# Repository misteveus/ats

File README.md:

# ats

## Remote
- 3.3v power and ground header
    - No OVP
    - No OCP
    - No polarity protection
    - Modules have their own decoupling caps
    - Modules have decoupling capacitors
- SPI header for LoRa module debug
- UART header for GPS module debug
- ICSP header for programming the PIC18
- LoRa module and SMD antenna
- GPS module and SMD antenna
- PIC18 controller
    - Controls SPI and UART

## References
Microcontroller PIC18F06Q40 [datasheet](https://ww1.microchip.com/downloads/aemDocuments/documents/MCU08/ProductDocuments/DataSheets/PIC18F06-16Q40-Data-Sheet-40002216D.pdf)  
LoRa Tranceiver RFM95W [datasheet](https://www.rfsolutions.co.uk/downloads/1463993415RFM95_96_97_98W.pdf)  
GPS/GLONASS Receiver YIC71009EBGG [datasheet](https://www.yic.com.tw/wp-content/uploads/2021/05/YIC71009EBGG.pdf)

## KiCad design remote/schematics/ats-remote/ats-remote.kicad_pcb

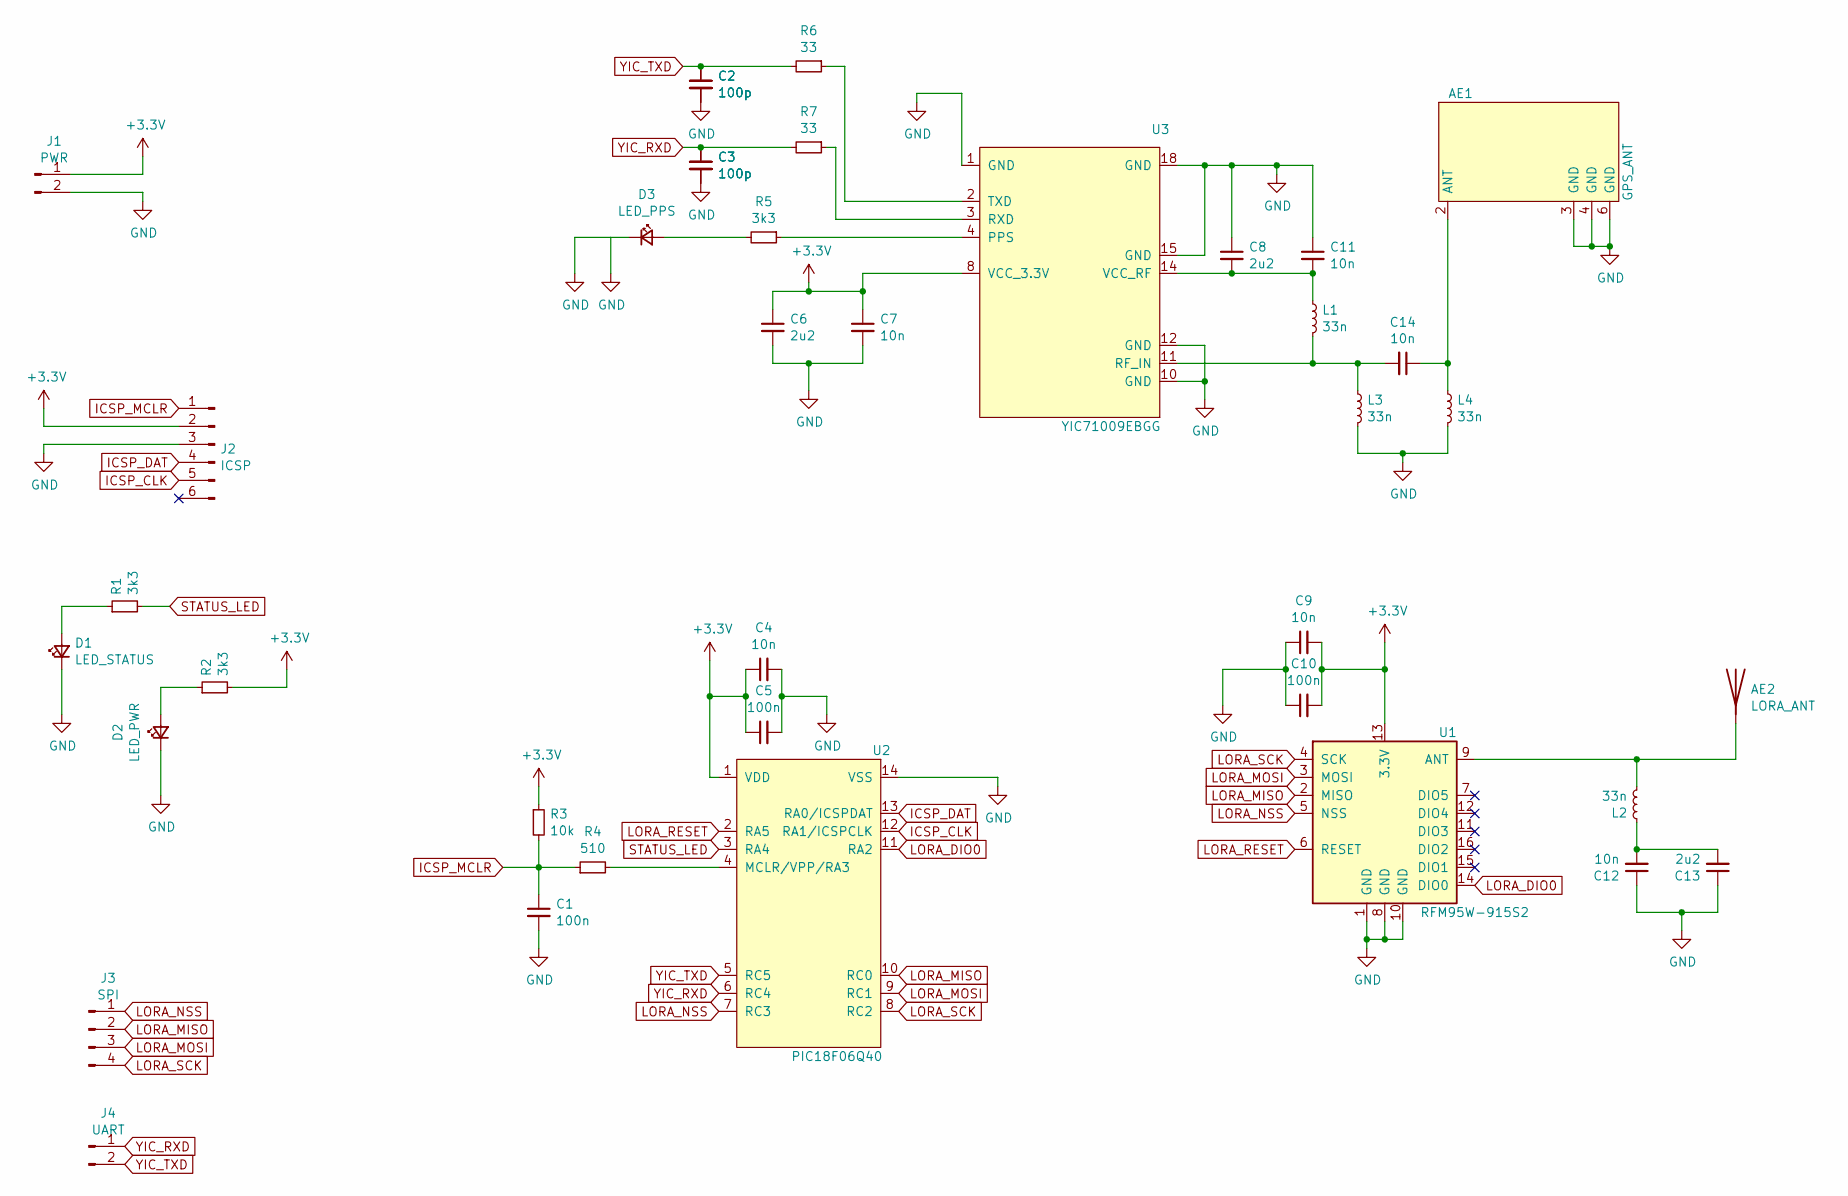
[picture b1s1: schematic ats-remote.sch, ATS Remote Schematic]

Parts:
AE1: GPS_ANT; GPS_ANT_SR4G008
AE2: LORA_ANT; LORA_ANT_YIC71009EBGG
C1, C5, C10: 100n; C_0805_2012Metric_Pad1.18x1.45mm_HandSolder
C2, C3: 100p; C_0805_2012Metric_Pad1.18x1.45mm_HandSolder
C4, C7, C9, C11, C12, C14: 10n; C_0805_2012Metric_Pad1.18x1.45mm_HandSolder
C6, C8, C13: 2u2; C_0805_2012Metric_Pad1.18x1.45mm_HandSolder
D1: LED_STATUS; D_1206_3216Metric_Pad1.42x1.75mm_HandSolder
D2: LED_PWR; D_1206_3216Metric_Pad1.42x1.75mm_HandSolder
D3: LED_PPS; D_1206_3216Metric_Pad1.42x1.75mm_HandSolder
J1: PWR; PinHeader_1x02_P1.27mm_Vertical
J2: ICSP; PinHeader_1x06_P1.27mm_Vertical
J3: SPI; PinHeader_1x04_P1.27mm_Vertical
J4: UART; PinHeader_1x02_P1.27mm_Vertical
L1, L2, L3, L4: 33n; L_0603_1608Metric_Pad1.05x0.95mm_HandSolder
R1, R2, R5: 3k3; R_1206_3216Metric_Pad1.30x1.75mm_HandSolder
R3: 10k; R_1206_3216Metric_Pad1.30x1.75mm_HandSolder
R4: 510; R_1206_3216Metric_Pad1.30x1.75mm_HandSolder
R6, R7: 33; R_1206_3216Metric_Pad1.30x1.75mm_HandSolder
U1: RFM95W-915S2; HOPERF_RFM9XW_SMD
U2: PIC18F06Q40; PIC18F06Q40-SOIC14
U3: YIC71009EBGG; YIC71009EBGG-19STAMP

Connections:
+3V3: C4.1, C5.1, C6.1, C7.1, C9.2, C10.2, J1.1, J2.2, R2.2, R3.1, U1.13 (3.3V), U2.1 (VDD), U3.8 (VCC_3.3V)
GND: AE1.3 (GND), AE1.4 (GND), AE1.6 (GND), C1.2, C2.2, C3.2, C4.2, C5.2, C6.2, C7.2, C8.1, C9.1, C10.1, C11.1, C12.1, C13.1, D1.1 (K), D2.1 (K), D3.1 (K), J1.2, J2.3, L3.2, L4.2, U1.1 (GND), U1.8 (GND), U1.10 (GND), U2.14 (VSS), U3.1 (GND), U3.10 (GND), U3.12 (GND), U3.15 (GND), U3.18 (GND)
ICSP_CLK: J2.5, U2.12 (RA1/ICSPCLK)
ICSP_DAT: J2.4, U2.13 (RA0/ICSPDAT)
ICSP_MCLR: C1.1, J2.1, R3.2, R4.1
LORA_DIO0: U1.14 (DIO0), U2.11 (RA2)
LORA_MISO: J3.2, U1.2 (MISO), U2.10 (RC0)
LORA_MOSI: J3.3, U1.3 (MOSI), U2.9 (RC1)
LORA_NSS: J3.1, U1.5 (NSS), U2.7 (RC3)
LORA_RESET: U1.6 (RESET), U2.2 (RA5)
LORA_SCK: J3.4, U1.4 (SCK), U2.8 (RC2)
unnamed: AE1.2 (ANT), C14.1, L4.1
unnamed: AE2.1, L2.2, U1.9 (ANT)
unnamed: C8.2, C11.2, L1.1, U3.14 (VCC_RF)
unnamed: C12.2, C13.2, L2.1
unnamed: C14.2, L1.2, L3.1, U3.11 (RF_IN)
unnamed: D1.2 (A), R1.1
unnamed: D2.2 (A), R2.1
unnamed: D3.2 (A), R5.2
unnamed: R4.2, U2.4 (MCLR/VPP/RA3)
unnamed: R5.1, U3.4 (PPS)
unnamed: R6.1, U3.2 (TXD)
unnamed: R7.1, U3.3 (RXD)
STATUS_LED: R1.2, U2.3 (RA4)
YIC_RXD: C3.1, J4.1, R7.2, U2.6 (RC4)
YIC_TXD: C2.1, J4.2, R6.2, U2.5 (RC5)

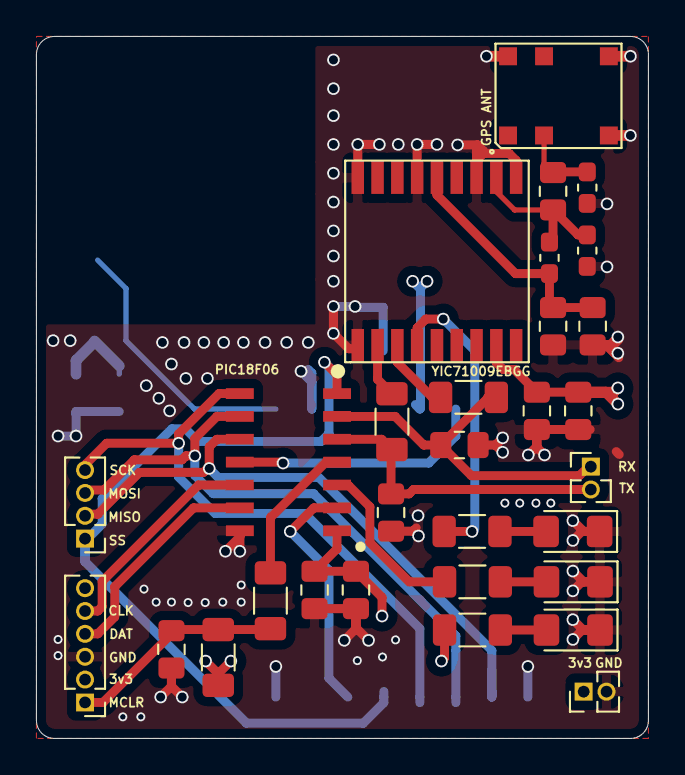
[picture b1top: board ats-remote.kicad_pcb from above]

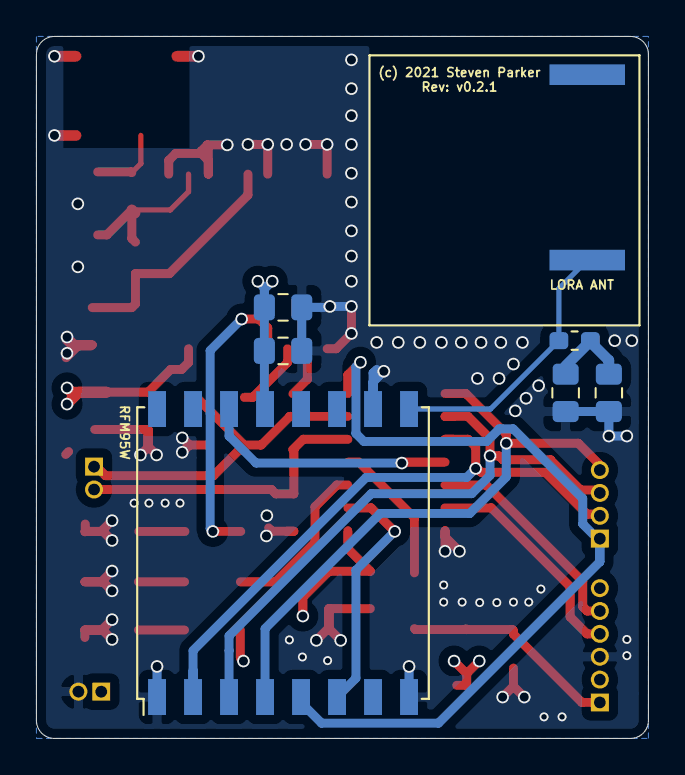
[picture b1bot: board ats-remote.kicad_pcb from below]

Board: 4 copper layers, 34.0 x 39.0 mm, 37 parts (7 on the bottom side), 26 nets.

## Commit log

2021-12-22 Update LICENSE
2021-12-22 Add initial directory structure
2021-12-22 Add main.c and initial device config
2021-12-22 Add webapp dependencies
2021-12-23 ignore bak files
2021-12-23 add kicad project files
2021-12-23 Add references
2021-12-23 ignore cache files
2021-12-23 add footprints, schematic, and pcb for breakout board
2021-12-23 move gitignore
2021-12-23 update gitignore
2021-12-23 add gerber files
2021-12-23 add schematic svg
2021-12-23 update schematic svg
2021-12-23 move gerber files to sub-directory and ignore autosave file
2021-12-24 add drill files
2021-12-25 add footprints for gps and lora antennas; start work on new board
2021-12-25 move remote schematic and pcb to v0.2.0 (#2)
    v0.2.0
    - 3.3v power and ground header
    - No OVP
    - No OCP
    - No polarity protection
    - Modules have their own decoupling caps
2021-12-25 remove gerber files
2021-12-27 update schematic and pcb
2021-12-27 add silk screen
2021-12-27 update silk screen
2021-12-27 fix lora nss via and gps ant grounds
2021-12-27 v0.2.1 (#3)
    * add footprints for gps and lora antennas; start work on new board
    * update schematic and pcb to v0.2.0
    * Update README.md
    * remove gerber files
    * update schematic and pcb
    * add silk screen
2021-12-27 update silkscreen to include copyright
2022-01-05 move driver module into the same src directory
2022-01-17 add MPLAB X project (#4)
    * move driver module into the same src directory
    * add MPLAB X project files
2022-01-17 add MPLAB X project files
2022-01-18 move io drivers to separate modules
2022-01-20 add module for interrupts
2022-01-20 update initerrupts init function to enable INT0 interrupt and priorities
2022-01-20 update interrupts init function to enable INT0 interrupt and priorities
2022-01-21 update spi1 init function and add declaration for sp1 send
2022-01-21 add spi1 send implementation
2022-01-22 update spi drivers to fix several bugs and add tmr0 interrupt handler for status led
2022-01-23 update resistor values to reflect those used on board
2022-01-23 Move timers to separate module
2022-01-23 fix SPI1 SDI input pin config. set all SPI1 pins to digital.
2022-01-24 add defines and helper functions for lora configurations
2022-05-17 update transmitter to test GPS module

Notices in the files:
remote/schematics/ats-remote/ats-remote.kicad_pcb:
(c) 2021 Steven Parker
